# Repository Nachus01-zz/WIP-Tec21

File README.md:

# Tec21
A Modular sensor system designed to be mounted on a rocket in order to gather, analyze and store flight data.

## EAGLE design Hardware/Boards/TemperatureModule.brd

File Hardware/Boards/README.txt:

Here you can view the Ealge board files for each of the boards.
The .zip file contains all other files in one download.

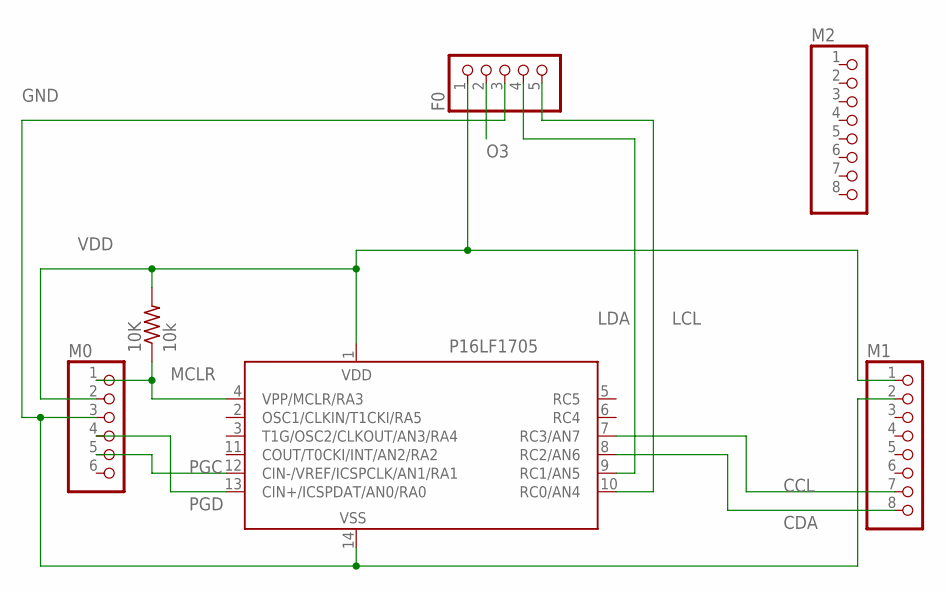
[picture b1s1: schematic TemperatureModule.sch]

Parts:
10K: 10k; 0204/7
F0: PINHD-1X5; 1X05
M0: PINHD-1X6; 1X06
M1, M2: PINHD-1X8; 1X08
P16LF1705: PIC16F676SL; SO-14

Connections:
CCL: M1.7, P16LF1705.7 (RC3/AN7)
CDA: M1.8, P16LF1705.8 (RC2/AN6)
GND: F0.3, M0.3, M1.2, P16LF1705.14 (VSS)
LCL: F0.5, P16LF1705.10 (RC0/AN4)
LDA: F0.4, P16LF1705.9 (RC1/AN5)
MCLR: 10K.1, M0.1, P16LF1705.4 (VPP/MCLR/RA3)
O3: F0.2
PGC: M0.5, P16LF1705.12 (CIN-/VREF/ICSPCLK/AN1/RA1)
PGD: M0.4, P16LF1705.13 (CIN+/ICSPDAT/AN0/RA0)
VDD: 10K.2, F0.1, M0.2, M1.1, P16LF1705.1 (VDD)

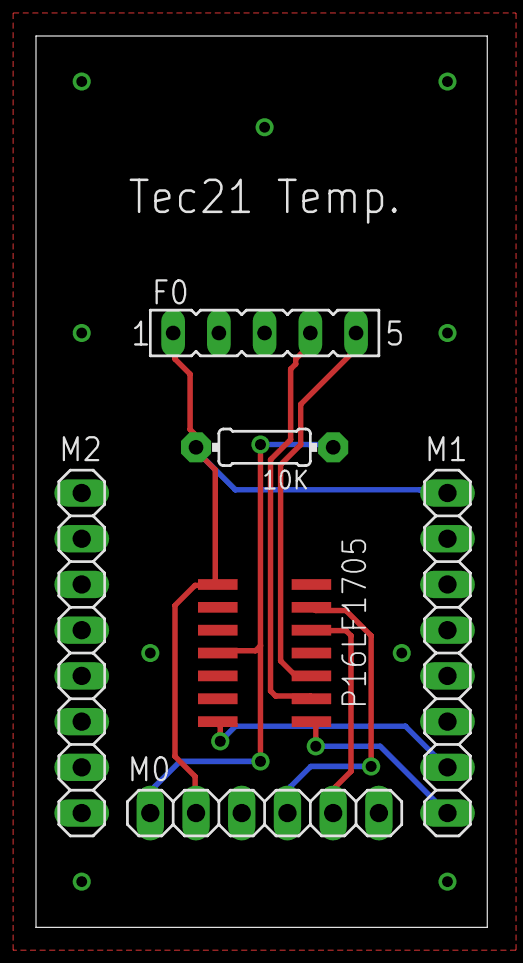
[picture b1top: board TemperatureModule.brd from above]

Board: 2 copper layers, 25.1 x 49.5 mm, 6 parts (0 on the bottom side), 9 nets.

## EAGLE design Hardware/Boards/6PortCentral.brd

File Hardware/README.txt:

This contains Hardware design files.
The Schematics folder contains schematic files, where you can view connection diagrams.
The Boards folder contains board files that can be used to manufacture PCBs.

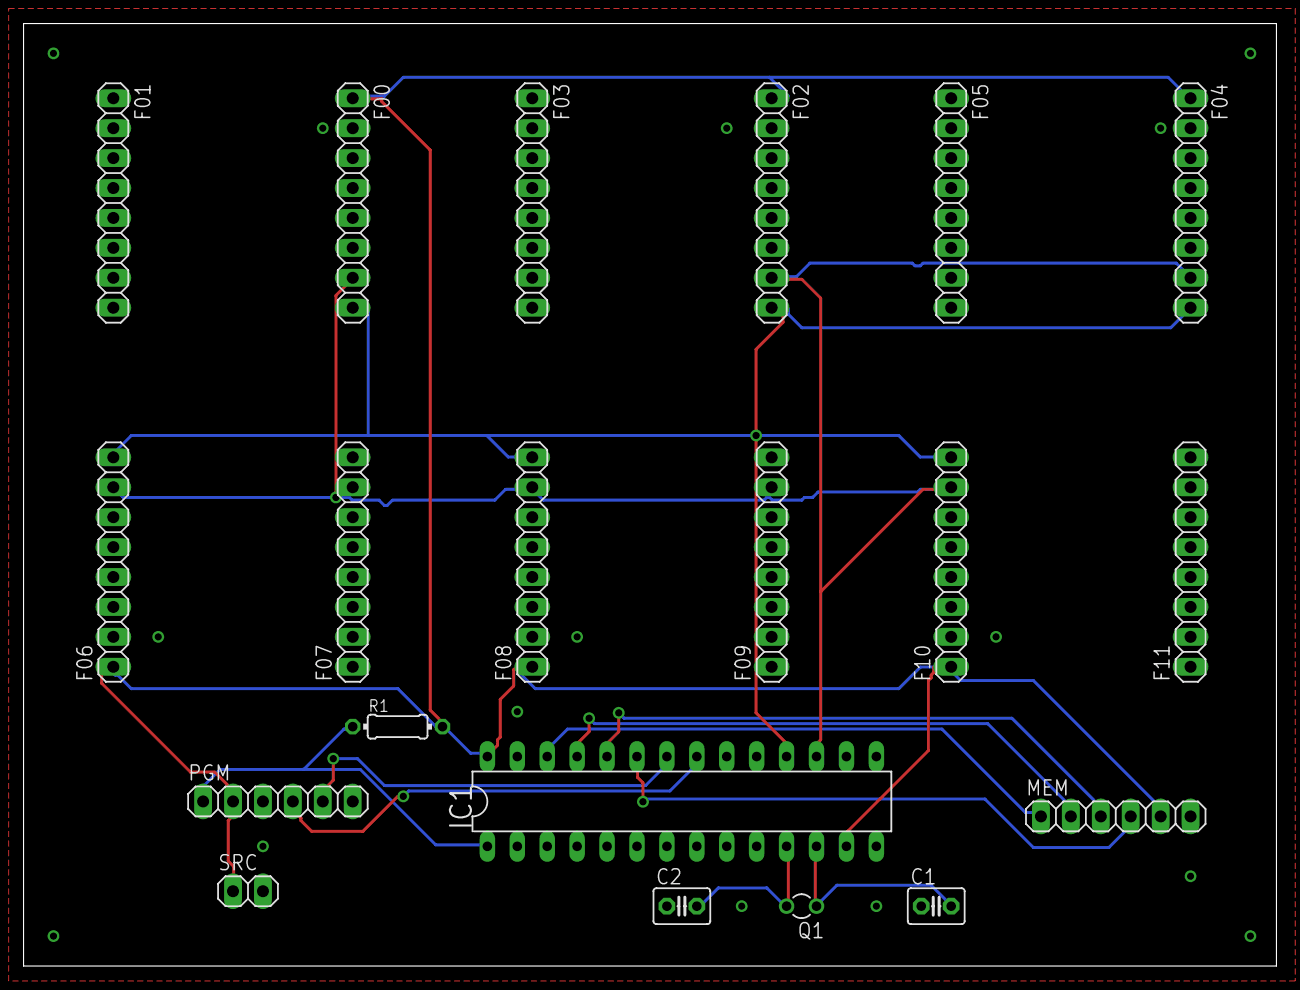
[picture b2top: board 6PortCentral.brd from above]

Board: 2 copper layers, 106.3 x 80.0 mm, 20 parts (0 on the bottom side), 13 nets.

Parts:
C1, C2: C025-030X050
F00, F01, F02, F03, F04, F05, F06, F07, F08, F09, F10, F11: 1X08
IC1: PIC24FJ64GA002; DIL28-3
MEM: 1X06
PGM: 1X06
Q1: TC26V
R1: 10k; 0204/7
SRC: 1X02

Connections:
GND: C1.1, C2.1, F00.2, F02.2, F04.2, F06.2, F08.2, F10.2, IC1.8, IC1.27, MEM.6, PGM.3, SRC.2
MISO: IC1.23, MEM.4
MOSI: IC1.24, MEM.3
unnamed: IC1.1, PGM.1, R1.1
unnamed: C1.2, IC1.12, Q1.1
unnamed: C2.2, IC1.11, Q1.2
unnamed: IC1.21, PGM.4
unnamed: IC1.22, PGM.5
SCL: F00.7, F02.7, F04.7, F06.7, F08.7, F10.7, IC1.17
SDA: F00.8, F02.8, F04.8, F06.8, F08.8, F10.8, IC1.18
SPICK: IC1.25, MEM.2
SS: IC1.26, MEM.1
VDD: F00.1, F02.1, F04.1, F06.1, F08.1, F10.1, IC1.13, IC1.28, MEM.5, PGM.2, R1.2, SRC.1

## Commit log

2016-11-07 Module (General)
    The .zip file contains an MPLab project for a general draft of one of the modules' software
2016-11-14 Create Template
2016-11-14 Create drme
